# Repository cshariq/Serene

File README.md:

# SERENE

Can't hear your friend talking on the highway? Do you need to blast your music just to hear it well? Well, you're in luck, because **Serene** is a portable noise-cancelling device that can remove all of that noise!

Just stick it to the roof of your car, and Serene will capture the road noise and output sounds waves that cancel them out, so that you can enjoy a peaceful car ride. 

Serene is a small, portable device that connects directly to your phone and car speaker. It sticks seamlessly to the walls of your car, and using ANC algorithms, it minimizes the external noise that it picks up inside the car.  

---

## Inspiration 

During family road trips, I sat in the backseat as a child, and if I didn't yell, my parents in the front couldn't hear me. This was so annoying, as a long highway drive almost always came with losing my voice. 

With my dad's hearing getting worse, I figured that we needed a way to drown out the road noise. I was desparate for a solution, so taking inspiration from noise-cancelling technology in headphones, I thought: "What if we did the same thing in cars?". 

While a few very luxury cars offer ANC, I wanted to make ANC more accessible to all people, because everyone deserves sereneness!

---

## How to use Serene

1. Click the power ON button at the top of the casing. 
2. Download the Serene app and pair your mobile device through Bluetooth / AUX / USB. 
3. Proceed with the calibration process.
4. Stick the Serene device anywhere in your car.
5. Turn the car on and start your peaceful drive.

---

## 3D Model: [OnShape Link](https://cad.onshape.com/documents/61c8b07b134ed299bc7b3a3e/w/ec2ebddc7aaece6417831267/e/c16017c5fc26cf24515a7a41?renderMode=0&uiState=69a0cfd834c79f4888558db4)

### PCB:

### Casing:

---

## PCB
### Main PCB

### Button PCB

---

## Wiring Diagram
### Main PCB

### Button PCB

---

## BOM
| Quantity | Part Name                               | Compoenent                                                    | Price(1 Quantity) | Total Price for all quantiy | Link                                                                              | Status    |
|----------|-----------------------------------------|---------------------------------------------------------------|-------------------|-----------------------------|-----------------------------------------------------------------------------------|-----------|
| 1        | WQFN-HR18__RYK_TEX                      | Power Chip                                                    | $2.48             | $2.48                       | https://jlcpcb.com/partdetail/TexasInstruments-BQ25620RYKR/C6164243               | In Stock  |
| 2        | CONN_X.FL-R-SMT-180_HIR                 | Coaxial Connector for bluetooth and UWB antennas              | $0.27             | $0.53                       | https://jlcpcb.com/partdetail/HRS_Hirose-X_FL_R_SMT_1_80/C434819                  | In Stock  |
| 17       | C_0402_1005Metric                       | Capacitor, 0.1uF                                              | $0.00             | $0.03                       | https://jlcpcb.com/partdetail/MurataElectronics-GRM155R71C104KA88D/C71629         | In Stock  |
| 1        | C_0402_1005Metric                       | Capacitor, 47nF                                               | $0.00             | $0.00                       | https://jlcpcb.com/partdetail/MurataElectronics-GRM155R71E473KA88D/C77017         | In Stock  |
| 1        | Spark_SR1120_QFN32                      | UWB Chip, used for audio transmission                         | $16.54            | $16.54                      | https://jlcpcb.com/partdetail/SPARKMicrosystems-SR1120AA_4Q32TR/C47090725         | Pre-Order |
| 1        | SOT-23-5                                | 1.8V Power Regulator                                          | $0.11             | $0.11                       | https://jlcpcb.com/partdetail/DiodesIncorporated-AP2112K_18TRG1/C176944           | In Stock  |
| 2        | Infineon_PG-LLGA-5-2                    | Mics                                                          | $10.28            | $20.56                      | https://www.aliexpress.com/item/1005009306016183.html?gatewayAdapt=4itemAdapt                                | In Stock  |
| 1        | USB_C_Receptacle_GCT_USB4085            | USB C Port (USB 2.0)                                          | $1.19             | $1.19                       | https://jlcpcb.com/partdetail/8061907-USB4085_GFA/C7095263                        | In Stock  |
| 1        | Jack_3.5mm_CUI_SJ2-3593D-SMT_Horizontal | Headphone Jack                                                | $11.30            | $11.30                      | https://jlcpcb.com/partdetail/CUI-SJ2_3593D_SMTTR/C4991621                        | In Stock  |
| 4        | R_0402_1005Metric                       | Resistor, 100kΩ                                               | $0.01             | $0.04                       | https://jlcpcb.com/partdetail/YAGEO-RC0402FR07100KL/C60491                        | In Stock  |
| 1        | STM32H743ZIT6                           | Microcontroller, STM32H743ZIT6                                | $8.19             | $8.19                       | https://jlcpcb.com/partdetail/STMicroelectronics-STM32H743ZIT6/C114408            | In Stock  |
| 7        | C_0402_1005Metric                       | Capacitor, 10uF                                               | $0.01             | $0.07                       | https://jlcpcb.com/partdetail/MurataElectronics-GRM155R60J106ME44D/C76991         | In Stock  |
| 1        | C_0402_1005Metric                       | Capacitor, 4.7µF                                              | $0.01             | $0.01                       | https://jlcpcb.com/partdetail/313626-GRM155R61A475MEAAD/C335105                   | In Stock  |
| 1        | ADXL382_Ultralib                        | Vibration Sensor, used for predicting sound                   | $28.05            | $28.05                      | https://jlcpcb.com/partdetail/AnalogDevices-ADXL382_1BCCZRL7/C41718413            | In Stock  |
| 1        | L_0603_1608Metric                       | Inductor, 180nH                                               | $0.09             | $0.09                       | https://jlcpcb.com/partdetail/MurataElectronics-LQW18ANR18G80D/C162650            | In Stock  |
| 1        | Crystal_SMD_3225-4Pin_3.2x2.5mm         | Crystal, 32.768 kHz                                           | $0.49             | $0.49                       | https://jlcpcb.com/partdetail/AbraconLLC-ABS07_32_768KHZT/C130253                 | In Stock  |
| 5        | C_0402_1005Metric                       | Capacitor, 1uF                                                | $0.01             | $0.05                       | https://jlcpcb.com/partdetail/MurataElectronics-GRM155R61A105KE15D/C76999         | In Stock  |
| 6        | C_0402_1005Metric                       | Capacitor, 10pF                                               | $0.01             | $0.06                       | https://jlcpcb.com/partdetail/MurataElectronics-GRM1555C1H100JA01D/C76946         | In Stock  |
| 1        | ADAU1787_Ultralib                       | DSP(Digital Signal Processor) used for processing sound       | $19.07            | $19.07                      | https://jlcpcb.com/partdetail/AnalogDevices-ADAU1787BCBZRL7/C3226201              | In Stock  |
| 1        | SOT-223-3_TabPin2                       | 3.3V Power Regulator                                          | $0.29             | $0.29                       | https://jlcpcb.com/partdetail/DiodesIncorporated-AP7361C_33E13/C500795            | In Stock  |
| 2        | R_0402_1005Metric                       | Resistor, 5.1k                                                | $0.01             | $0.02                       | https://jlcpcb.com/partdetail/YAGEO-RC0402FR075K1L/C105872                        | In Stock  |
| 1        | L_0603_1608Metric                       | Inductor, 1.5uH                                               | $0.10             | $0.10                       | https://jlcpcb.com/partdetail/MurataElectronics-DFE252012F_1R5MP2/C909806         | In Stock  |
| 1        | BGM220S_SIL                             | Bluetooth Chip                                                | $13.84            | $13.84                      | https://jlcpcb.com/partdetail/1603489-BGM220SC12WGA2R/C1512693                    | Pre-Order |
| 1        | Crystal_SMD_3225-4Pin_3.2x2.5mm         | Crystal                                                       | $0.08             | $0.08                       | https://jlcpcb.com/partdetail/YXC_CrystalOscillators-X322525MQB4SI/C70585         | In Stock  |
| 1        | Balun_Johanson_1.6x0.8mm                | Transformer                                                   | $8.97             | $8.97                       | https://jlcpcb.com/partdetail/YXC_CrystalOscillators-X322525MQB4SI/C70585         | In Stock  |
| 2        | R_0402_1005Metric                       | Resistor, 2.2kΩ                                               | $0.01             | $0.02                       | https://jlcpcb.com/partdetail/YAGEO-RC0402FR072K2L/C114762                        | In Stock  |
| 1        | R_0402_1005Metric                       | Resistor, 170Ω                                                | $0.01             | $0.01                       | https://jlcpcb.com/partdetail/YAGEO-RC0402FR07180RL/C138045                       | In Stock  |
| 5        | R_0402_1005Metric                       | Resistor, 10kΩ                                                | $0.01             | $0.05                       | https://jlcpcb.com/partdetail/YAGEO-RC0402FR0710KL/C60490                         | In Stock  |
| 2        | C_0402_1005Metric                       | Capacitor, 2.2uF                                              | $0.01             | $0.02                       | https://jlcpcb.com/partdetail/MurataElectronics-GRM155R61A225KE95D/C77002         | In Stock  |
| 1        | SOT-23-6                                | ESD protection diode, used for headphone jack                 | $0.13             | $0.13                       | https://jlcpcb.com/partdetail/STMicroelectronics-USBLC62SC6/C7519                 | In Stock  |
| 2        | CONN_503480-0540_MOL                    | Molex connector used for linking button PCB with main PCB     | $0.83             | $1.66                       | https://jlcpcb.com/partdetail/MOLEX-5034800540/C5527934                           | In Stock  |
| 3        | LED_SK6805_PLCC4_2.4x2.7mm_P1.3mm       | LEDS on the Button PCB                                        | $3.95             | $11.86                      | https://www.adafruit.com/product/4492                                             | In Stock  |
| 1        | SW_Push_1P1T_NO_CK_KMR2                 | Button on the Button PCB                                      | $0.61             | $0.61                       | https://jlcpcb.com/partdetail/CK-KMR221GLFS/C72443                                | In Stock  |
| 1        | Vapcell N40                             | Battery                                                       | $20.00            | $20.00                      | https://www.vapcelltech.com/h-pd-193.html                                         | In Stock  |
| 1        | N/A                                     | Nickel Strips used for connecting the + and - of the battery  | $6.45             | $6.45                       | https://www.amazon.ca/Nickel-Plated-Connection-Refined-Welding/dp/B0CPFL5ZWM/     | In Stock  |
| 1        | N/A                                     | Pair of Pogo Pins                                             | $6.06             | $6.06                       | https://www.amazon.ca/Connector-Positions-Pogopin-Contact-3PIN/dp/B0BXDFJVVZ?th=1 | In Stock  |
| 1        | N/A                                     | uxcell 45mm x 0.5mm 6 Pin FPC/FFC Flat Ribbon Cable Connector | $9.99             | $9.99                       | https://www.amazon.ca/gp/product/B00H8PCW06                                       |           |
| 1        | N/A                                     | N/A                                                           | $53.85            | $53.85                      |                                                                                   |           |
| 1        | N/A                                     | N/A                                                           | $7.20             | $7.20                       |                                                                                   |           |

| Subtotal               | Source       | Notes                                                                                                                                                                    |
|------------------------|--------------|--------------------------------------------------------------------------------------------------------------------------------------------------------------------------|
| $228.21                | JLCPCB Parts | 2x (JLCPCB requires 2 of each part)                                                                                                                                      |
| $61.05                 | JLCPCB PCB   | 0.15mm via and epoxy filled & capped selectedas it is required by the ADAU1787 Chip. Lead free coating also selected for safety and its only a dollar extra. 6 Layer manufacturing is selected because it is cheaper than 2/4 layer manufacturing due to a coupon. Although other options were explored, most DSPs(Digital Singal Processors) which is required for fast processing of audio(required for ANC) are WLCSP chips requiring 0.15mm vias which are epoxy filled & capped. Other solutions are too slow for this application.|
| $22.50                 | Amazon       |                                                                                                                                                                          |
| $20.56                 | AliExpress   |                                                                                                                                                                          |
| $11.86                 | Adafruit     | For the LEDs                                                                                                                                                             |
| $250.08                | All          | Not accounting for 2x JLCPCB Parts                                                                                                                                       |
| $364.18                | All          | 2x (JLCPCB required 2 of each part)                                                                                                                                      |

| Grand Total            | Price        | Notes                                                                                                                                                                    |
|------------------------|--------------|--------------------------------------------------------------------------------------------------------------------------------------------------------------------------|
| JLCParts Grand Total   | $238.13      | 2x (JLCPCB required 2 of each part)                                                                                                                                      |
| JLCPCB Grand Total     | $72.25       | JLCPCB Advanced is cheaper due to coupons                                                                                                                                |
| Amazon Subtotal        | $16.28       | 22.5 CAD --> 16.28 USD                                                                                                                                                   |
| Adafruit Grand Total   | $23.08       |                                                                                                                                                                          |
| AliExpress Grand Total | $20.70       | 28.07 CAD --> 20.70 USD                                                                                                                                                  |
| Vapcell Grand Total    | $22.99       |                                                                                                                                                                          |
| Grand Total            | $393.43      |                                                                                                                                                                          |

### Screenshots of total with shipping and taxes.

Amazon:

JLCPCB Parts:

JLCPCB PCB (6 layer manufacturing for Main PCB, less expensive):

JLCPCB PCB (4 layer manufacturing for Main PCB, more expensive and thus **not used**)

Button PCB:

AliExpress:

Vapcell:

Adafruit:

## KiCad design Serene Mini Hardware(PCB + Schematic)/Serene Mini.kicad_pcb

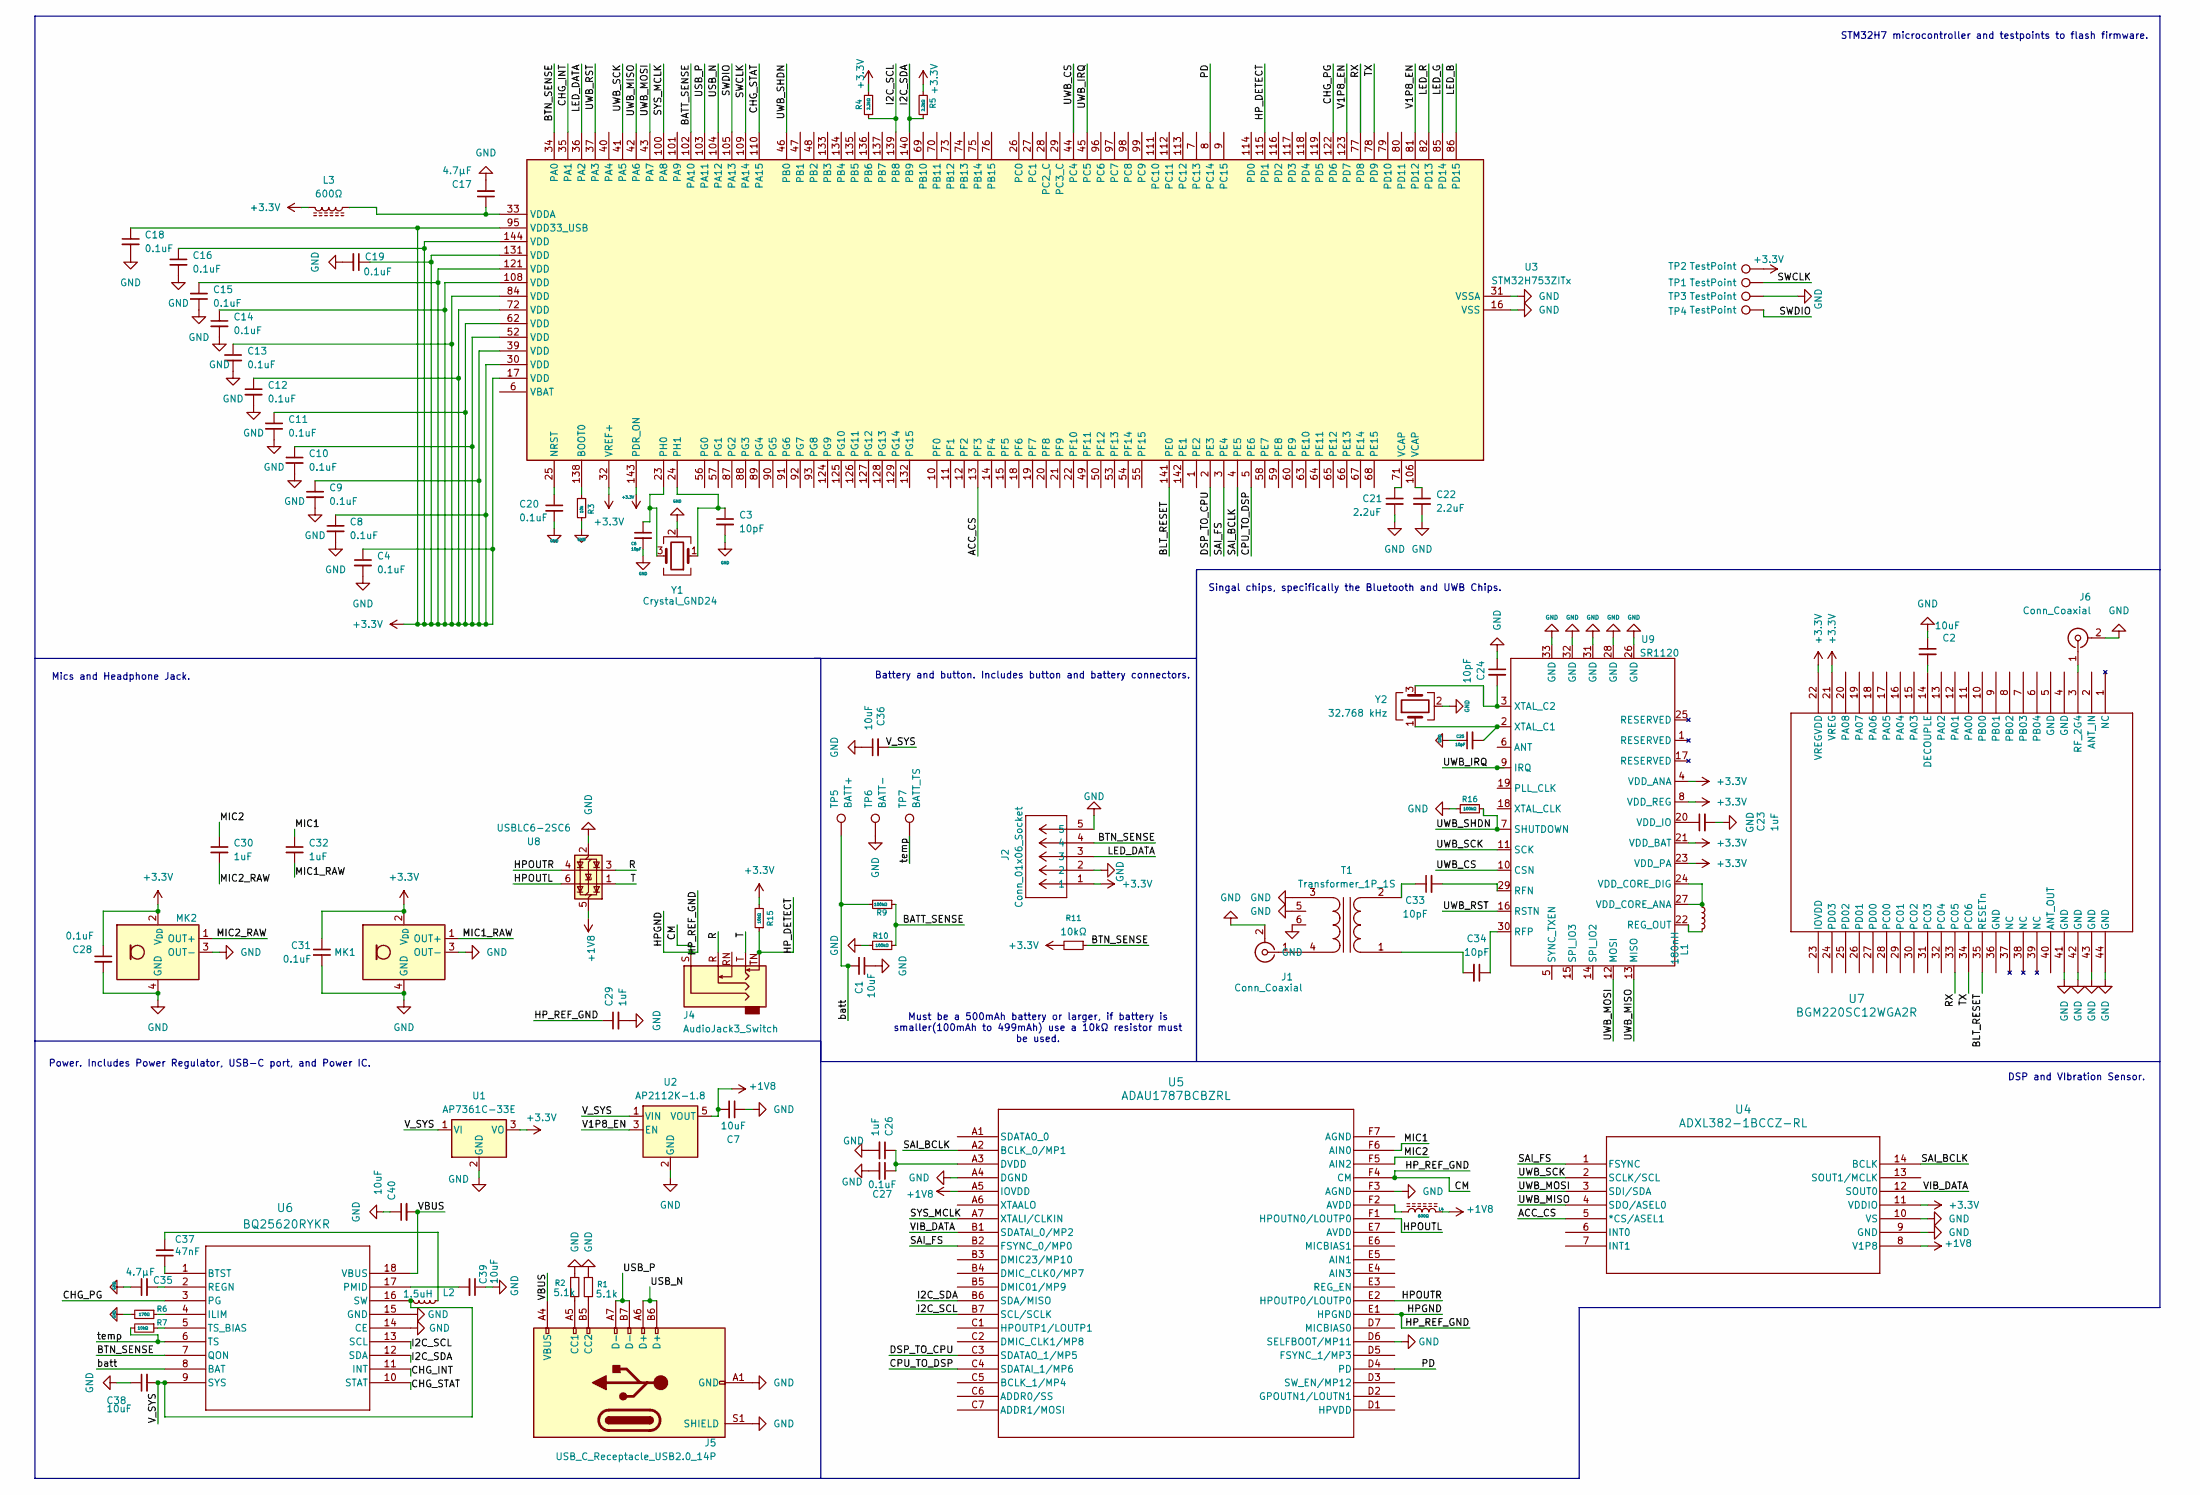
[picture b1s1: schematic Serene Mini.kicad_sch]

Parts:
C1, C2, C7, C36, C38, C39, C40: 10uF; C_0402_1005Metric
C3, C6, C24, C25, C33, C34: 10pF; C_0402_1005Metric
C4, C8, C9, C10, C11, C12, C13, C14, C15, C16, C18, C19, C20, C27, C28, C31: 0.1uF; C_0402_1005Metric
C17, C35: 4.7µF; C_0402_1005Metric
C21, C22: 2.2uF; C_0402_1005Metric
C23, C26, C29, C30, C32: 1uF; C_0402_1005Metric
C37: 47nF; C_0402_1005Metric
J1, J6: Conn_Coaxial; CONN_X.FL-R-SMT-180_HIR
J2: Conn_01x06_Socket; CONN_503480-0540_MOL
J4: AudioJack3_Switch; Jack_3.5mm_CUI_SJ2-3593D-SMT_Horizontal
J5: USB_C_Receptacle_USB2.0_14P; USB_C_Receptacle_GCT_USB4085
L1: 180nH; L_0603_1608Metric
L2: 1.5uH; L_0603_1608Metric
L3, L4: 600Ω; L_0402_1005Metric
MK1, MK2: IM73A135V01; Infineon_PG-LLGA-5-2
R1, R2: 5.1k; R_0402_1005Metric
R3: 10k; R_0402_1005Metric
R4, R5: 2.2kΩ; R_0402_1005Metric
R6: 170Ω; R_0402_1005Metric
R7, R11, R15: 10kΩ; R_0402_1005Metric
R9, R10, R16: 100kΩ; R_0402_1005Metric
T1: Transformer_1P_1S; Balun_Johanson_1.6x0.8mm
TP1, TP2, TP3, TP4: TestPoint; TestPoint_Pad_1.0x1.0mm
TP5: BATT+; SolderWirePad_1x01_SMD_1x2mm
TP6: BATT-; SolderWirePad_1x01_SMD_1x2mm
TP7: BATT_TS; SolderWirePad_1x01_SMD_1x2mm
U1: AP7361C-33E; SOT-223-3_TabPin2
U2: AP2112K-1.8; SOT-23-5
U3: STM32H753ZITx; LQFP-144_20x20mm_P0.5mm
U4: ADXL382-1BCCZ-RL; ADXL382_Ultralib
U5: ADAU1787BCBZRL; ADAU1787_Ultralib
U6: BQ25620RYKR; WQFN-HR18__RYK_TEX
U7: BGM220SC12WGA2R; BGM220S_SIL
U8: USBLC6-2SC6; SOT-23-6
U9: SR1120; Spark_SR1120_QFN32
Y1: Crystal_GND24; Crystal_SMD_3225-4Pin_3.2x2.5mm
Y2: 32.768 kHz; Crystal_SMD_3225-4Pin_3.2x2.5mm

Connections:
+1V8: C7.2, L4.2, U2.5 (VOUT), U4.8 (V1P8), U5.A5 (IOVDD), U8.5 (VBUS)
+3.3V: C4.1, C8.1, C9.1, C10.1, C11.1, C12.1, C13.1, C14.1, C15.1, C16.1, C18.1, C19.1, C28.1, C31.1, J2.1, L3.2, MK1.2 (V_{DD}), MK2.2 (V_{DD}), R4.2, R5.2, R11.2, R15.2, TP1.1, U1.3 (VO), U3.17 (VDD), U3.30 (VDD), U3.32 (VREF+), U3.39 (VDD), U3.52 (VDD), U3.62 (VDD), U3.72 (VDD), U3.84 (VDD), U3.95 (VDD33_USB), U3.108 (VDD), U3.121 (VDD), U3.131 (VDD), U3.143 (PDR_ON), U3.144 (VDD), U4.11 (VDDIO), U7.21 (VREG), U7.22 (VREGVDD), U9.4 (VDD_ANA), U9.8 (VDD_REG), U9.21 (VDD_BAT), U9.23 (VDD_PA)
/ACC_CS: U3.13 (PF3), U4.5 (*CS/ASEL1)
/BATT_SENSE: R9.1, R10.1, U3.102 (PA10)
/BLT_RESET: U3.141 (PE0), U7.35 (RESETn)
/BTN_SENSE: J2.4, R11.1, U3.34 (PA0), U6.7 (QON)
/CHG_INT: U3.35 (PA1), U6.11 (INT)
/CHG_PG: U3.122 (PD6), U6.3 (PG)
/CHG_STAT: U3.110 (PA15), U6.10 (STAT)
/CM: C29.1, J4.S, U5.E1 (HPGND), U5.F4 (CM)
/CPU_TO_DSP: U3.5 (PE6), U5.C4 (SDATAI_1/MP6)
/DSP_TO_CPU: U3.2 (PE3), U5.C3 (SDATAO_1/MP5)
/HPOUTL: U5.F1 (HPOUTN0/LOUTP0), U8.6 (I/O1)
/HPOUTR: U5.E2 (HPOUTP0/LOUTP0), U8.4 (I/O2)
/HP_DETECT: J4.TN, R15.1, U3.115 (PD1)
/I2C_SCL: R4.1, U3.139 (PB8), U5.B7 (SCL/SCLK), U6.13 (SCL)
/I2C_SDA: R5.1, U3.140 (PB9), U5.B6 (SDA/MISO), U6.12 (SDA)
/LED_B: U3.86 (PD15)
/LED_DATA: J2.3, U3.36 (PA2)
/LED_G: U3.85 (PD14)
/LED_R: U3.82 (PD13)
/MIC1: C32.1, U5.F6 (AIN0)
/MIC1_RAW: C32.2, MK1.1 (OUT+)
/MIC2: C30.1, U5.F5 (AIN2)
/MIC2_RAW: C30.2, MK2.1 (OUT+)
/PD: U3.8 (PC14), U5.D4 (PD)
/R: J4.R, U8.3 (I/O2)
/RX: U3.77 (PD8), U7.33 (PC05)
/SAI_BCLK: U3.4 (PE5), U4.14 (BCLK), U5.A2 (BCLK_0/MP1)
/SAI_FS: U3.3 (PE4), U4.1 (FSYNC), U5.B2 (FSYNC_0/MP0)
/SWCLK: TP2.1, U3.109 (PA14)
/SWDIO: TP4.1, U3.105 (PA13)
/SYS_MCLK: U3.100 (PA8), U5.A7 (XTALI/CLKIN)
/T: J4.T, U8.1 (I/O1)
/TX: U3.78 (PD9), U7.34 (PC06)
/USB_N: J5.A6 (D+), J5.B6 (D+), U3.104 (PA12)
/USB_P: J5.A7 (D-), J5.B7 (D-), U3.103 (PA11)
/UWB_CS: U3.44 (PC4), U9.10 (CSN)
/UWB_IRQ: U3.45 (PC5), U9.9 (IRQ)
/UWB_MISO: U3.42 (PA6), U4.4 (SDO/ASEL0), U9.13 (MISO)
/UWB_MOSI: U3.43 (PA7), U4.3 (SDI/SDA), U9.12 (MOSI)
/UWB_RST: U3.37 (PA3), U9.16 (RSTN)
/UWB_SCK: U3.41 (PA5), U4.2 (SCLK/SCL), U9.11 (SCK)
/UWB_SHDN: R16.2, U3.46 (PB0), U9.7 (SHUTDOWN)
/V1P8_EN: U2.3 (EN), U3.81 (PD12), U3.123 (PD7)
/VBUS: C40.2, J5.A4 (VBUS), J5.A9 (VBUS), J5.B4 (VBUS), J5.B9 (VBUS), U6.18 (VBUS)
/VIB_DATA: U4.12 (SOUT0), U5.B1 (SDATAI_0/MP2)
/V_SYS: C36.2, C38.2, L2.2, U1.1 (VI), U2.1 (VIN), U6.9 (SYS), U6.16 (SW)
/batt: C1.2, R9.2, TP5.1, U6.8 (BAT)
/temp: R7.2, TP7.1, U6.6 (TS)
GND: C1.1, C2.1, C3.2, C4.2, C6.2, C7.1, C8.2, C9.2, C10.2, C11.2, C12.2, C13.2, C14.2, C15.2, C16.2, C17.2, C18.2, C19.2, C20.2, C21.2, C22.2, C23.2, C24.1, C25.1, C26.2, C27.2, C28.2, C29.2, C31.2, C35.1, C36.1, C38.1, C39.1, C40.1, J1.2 (Ext), J2.2, J2.5, J5.A1 (GND), J5.A12 (GND), J5.B1 (GND), J5.B12 (GND), J5.S1 (SHIELD), J6.2 (Ext), MK1.3 (OUT-), MK1.4 (GND), MK1.5 (GND), MK2.3 (OUT-), MK2.4 (GND), MK2.5 (GND), R1.1, R2.1, R3.2, R6.2, R10.2, R16.1, T1.3 (SA), T1.5 (GND), T1.6 (GND), TP3.1, TP6.1, U1.2 (GND), U2.2 (GND), U3.16 (VSS), U3.31 (VSSA), U3.38 (VSS), U3.51 (VSS), U3.61 (VSS), U3.83 (VSS), U3.94 (VSS), U3.107 (VSS), U3.120 (VSS), U3.130 (VSS), U4.9 (GND), U4.10 (VS), U5.A4 (DGND), U5.D6 (SELFBOOT/MP11), U5.F3 (AGND), U6.1 (BTST), U6.5 (TS_BIAS), U6.10 (STAT), U6.14 (CE), U6.15 (GND), U7.41 (GND), U7.42 (GND), U7.43 (GND), U7.44 (GND), U8.2 (GND), U9.26 (GND), U9.28 (GND), U9.31 (GND), U9.32 (GND), U9.33 (GND), Y1.2 (G), Y1.4 (G), Y2.2 (G), Y2.4 (G)
unnamed: C21.1, U3.71 (VCAP)
unnamed: C22.1, U3.106 (VCAP)
unnamed: C37.2, L2.1
unnamed: J1.1 (In), T1.4 (SB)
unnamed: J5.A5 (CC1), R2.2
unnamed: J5.B5 (CC2), R1.2
unnamed: J6.1 (In), U7.3 (RF_2G4)
unnamed: L4.1, U5.F2 (AVDD)
unnamed: C34.2, T1.1 (AA)
unnamed: C33.1, T1.2 (AB)
unnamed: R3.1, U3.138 (BOOT0)
unnamed: C20.1, U3.25 (NRST)
unnamed: C6.1, U3.23 (PH0), Y1.3
unnamed: C3.1, U3.24 (PH1), Y1.1
unnamed: C17.1, L3.1, U3.33 (VDDA)
unnamed: C26.1, C27.1, U5.A3 (DVDD)
unnamed: C37.1, U6.1 (BTST)
unnamed: R6.1, U6.4 (ILIM)
unnamed: C39.2, U6.17 (PMID)
unnamed: C35.2, U6.2 (REGN)
unnamed: R7.1, U6.5 (TS_BIAS)
unnamed: C2.2, U7.14 (DECOUPLE)
unnamed: L1.2, U9.22 (REG_OUT)
unnamed: C33.2, U9.29 (RFN)
unnamed: C34.1, U9.30 (RFP)
unnamed: L1.1, U9.24 (VDD_CORE_DIG), U9.27 (VDD_CORE_ANA)
unnamed: C23.1, U9.20 (VDD_IO)
unnamed: C25.2, U9.2 (XTAL_C1), Y2.1
unnamed: C24.2, U9.3 (XTAL_C2), Y2.3

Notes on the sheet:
Must be a 500mAh battery or larger, if battery is smaller(100mAh to 499mAh) use a 10kΩ resistor must be used.
STM32H7 microcontroller and testpoints to flash firmware.
Battery and button. Includes button and battery connectors.
DSP and VIbration Sensor.
Power. Includes Power Regulator, USB-C port, and Power IC.
Singal chips, specifically the Bluetooth and UWB Chips.
Mics and Headphone Jack.

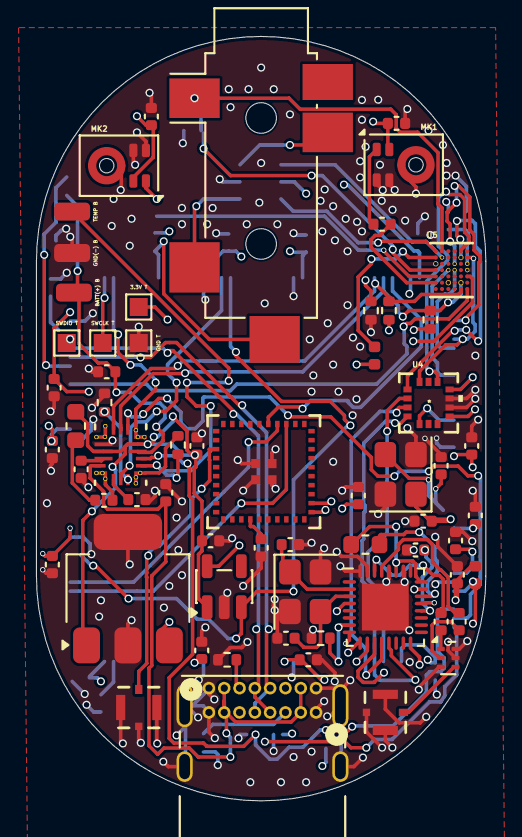
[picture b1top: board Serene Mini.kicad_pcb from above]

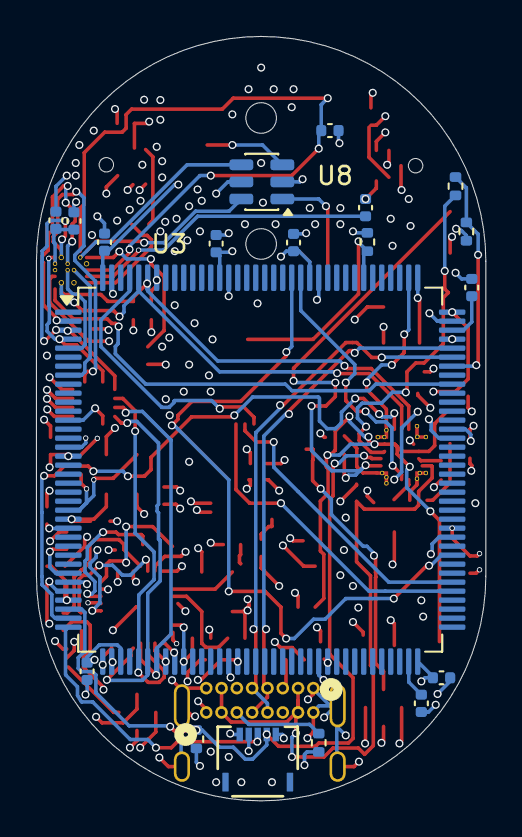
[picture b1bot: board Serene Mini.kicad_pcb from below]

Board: 6 copper layers, 25.0 x 42.5 mm, 81 parts (19 on the bottom side), 77 nets.

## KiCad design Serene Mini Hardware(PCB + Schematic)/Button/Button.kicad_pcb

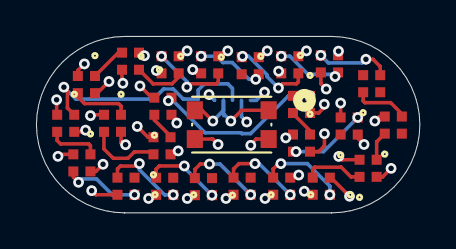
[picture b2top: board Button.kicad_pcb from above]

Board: 4 copper layers, 21.3 x 9.8 mm, 26 parts (1 on the bottom side), 27 nets.

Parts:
D1, D2, D3, D4, D5, D6, D7, D8, D9, D10, D11, D12, D13, D14, D15, D16, D17, D18, D19, D20, D21, D22, D23, D24: SK6805; IPIXEL SK6805-E-J_ADA
J2: Conn_01x06_Socket; CONN_503480-0540_MOL
SW1: SW_Push; SW_Push_1P1T_NO_CK_KMR2

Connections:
+3.3V: D1.2 (VDD), D2.2 (VDD), D3.2 (VDD), D4.2 (VDD), D5.2 (VDD), D6.2 (VDD), D7.2 (VDD), D8.2 (VDD), D9.2 (VDD), D10.2 (VDD), D11.2 (VDD), D12.2 (VDD), D13.2 (VDD), D14.2 (VDD), D15.2 (VDD), D16.2 (VDD), D17.2 (VDD), D18.2 (VDD), D19.2 (VDD), D20.2 (VDD), D21.2 (VDD), D22.2 (VDD), D23.2 (VDD), D24.2 (VDD), J2.1
/BTN_SENSE: J2.4, SW1.1
/LED_DATA: D1.1 (DIN), J2.3
GND: D1.4 (GND), D2.4 (GND), D3.4 (GND), D4.4 (GND), D5.4 (GND), D6.4 (GND), D7.4 (GND), D8.4 (GND), D9.4 (GND), D10.4 (GND), D11.4 (GND), D12.4 (GND), D13.4 (GND), D14.4 (GND), D15.4 (GND), D16.4 (GND), D17.4 (GND), D18.4 (GND), D19.4 (GND), D20.4 (GND), D21.4 (GND), D22.4 (GND), D23.4 (GND), D24.4 (GND), J2.2, J2.5, SW1.2
unnamed: D1.3 (DOUT), D2.1 (DIN)
unnamed: D2.3 (DOUT), D3.1 (DIN)
unnamed: D3.3 (DOUT), D4.1 (DIN)
unnamed: D4.3 (DOUT), D5.1 (DIN)
unnamed: D5.3 (DOUT), D6.1 (DIN)
unnamed: D6.3 (DOUT), D7.1 (DIN)
unnamed: D7.3 (DOUT), D8.1 (DIN)
unnamed: D8.3 (DOUT), D9.1 (DIN)
unnamed: D9.3 (DOUT), D10.1 (DIN)
unnamed: D10.3 (DOUT), D11.1 (DIN)
unnamed: D11.3 (DOUT), D12.1 (DIN)
unnamed: D12.3 (DOUT), D13.1 (DIN)
unnamed: D13.3 (DOUT), D14.1 (DIN)
unnamed: D14.3 (DOUT), D15.1 (DIN)
unnamed: D15.3 (DOUT), D16.1 (DIN)
unnamed: D16.3 (DOUT), D17.1 (DIN)
unnamed: D17.3 (DOUT), D18.1 (DIN)
unnamed: D18.3 (DOUT), D19.1 (DIN)
unnamed: D19.3 (DOUT), D20.1 (DIN)
unnamed: D20.3 (DOUT), D21.1 (DIN)
unnamed: D21.3 (DOUT), D22.1 (DIN)
unnamed: D22.3 (DOUT), D23.1 (DIN)
unnamed: D23.3 (DOUT), D24.3 (DOUT)

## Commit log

2025-12-22 Created Structure for Dart App
2025-12-22 Initial App UI
2025-12-23 Updated UI
2025-12-24 Bug Fixes
2025-12-28 Redesigned vehicle and sound menu
2026-01-05 Implement vehicle selection screen with custom vehicle addition
    - Added VehicleSelectionScreen for selecting and adding vehicles.
    - Integrated search functionality for vehicle models.
    - Implemented dialog for adding custom vehicles with type selection.
    - Enhanced vehicle selection logic with existing vehicle handling.
    - Added validation for device limits based on vehicle type.
    Introduce ANC audio output service
2026-01-13 Add GitHub Actions workflow for Dart CI
2026-01-13 Update dart.yml to include path filters
    Add path filters for push and pull_request events
2026-01-13 Update dart.yml to include paths for serene directory
    Specify paths for push and pull_request events.
2026-01-13 Update README to remove introductory line
    Removed introductory line about the project being a new Flutter project.
2026-01-13 Refactor Dart CI workflow for clarity and structure
2026-01-13 Add project description to README
    Added a brief description of the project.
2026-01-13 Switch Dart commands to Flutter in CI workflow
2026-01-13 Update Dart workflow to use Flutter setup
2026-01-13 Fix formatting in README.md
2026-01-15 Refactor Flutter CI/CD workflow for better structure
2026-01-19 Added support for battery
2026-01-20 PCB and Schematic Design Changes
    Upgraded to the newer sr1120
    Reduced the PCB size by ~40%
    More efficient layout with chips on both side of the pcb
2026-01-23 Final PCB and Schematic Design
    - Added new IC to support fast charging for batteries up to 3000mAh
    - Added a bluetooth chip
    - Used smaller coaxial ports to increase available space
    - The button is now located off the board connected via molax
    - Finished routing
2026-01-23 PCB Fixes
    Connected some missing traces and fixed some clearance issues
2026-01-23 Footprint Fixes
    Added/linked a 3D model to the molex connector.
2026-01-23 Changed Footprint
    Added cooling and repositioned the testpoint pads to be closer ti each other
2026-01-28 Minor Changes
    - Fixed minor issues in the PCB like routing the USB data lines parallel
    - Added BOM
    - Added blueprint folder containing everything required
2026-01-28 Added Checkout Screenshots
2026-01-28 Added Documentation and Drill files
2026-02-02 Minor Changes
2026-02-05 Add initial README for Serene
    Added a detailed description of the Serene noise-cancelling device, including its inspiration, usage instructions, and sections for 3D model, PCB, wiring diagram, and BOM.
2026-02-05 Clean up README formatting
    Removed extra line breaks in PCB and Wiring Diagram sections.
2026-02-05 Add images for PCB and Casing in README
    Added images for PCB and Casing sections in README.
2026-02-05 fixed formatting
2026-02-05 Add detailed BOM to README
    Added a detailed Bill of Materials (BOM) with component specifications, quantities, prices, and sources.
2026-02-05 fixed formatting #2
2026-02-05 File Structure Changes
2026-02-05 change image sizes
2026-02-06 Enhance PCB selection explanation in README
    Expanded details on PCB selection and alternatives for DSPs.
2026-02-06 Revise PCB cost details and format screenshots section
    Updated PCB manufacturing details and changed heading format for screenshots.
2026-02-06 Update PCB manufacturing description in README
2026-02-06 Clean up image entries in README.md
    Removed unnecessary image entries from the README.
2026-02-06 Add supplier screenshots to README
    Added screenshots for various suppliers including Amazon, AliExpress, Vapcell, and Adafruit.
2026-02-06 Add images and descriptions to README
2026-02-06 Add grand total section to README
2026-02-06 Update 'Source' to 'Price' in README table
2026-02-06 Revise JLCPCB PCB descriptions in README
    Updated descriptions for JLCPCB PCB images to clarify manufacturing layers and costs.
2026-02-06 Changes to File Structure
    - Removed redundant blueprint folder
    - Made folder names more clear
2026-02-07 Added Stitching Vias
2026-02-07 Changes to PCB
    - Added 2 more filled zones, 1 on layer 3 and 4 respectively
    - Added stitching vias
    - Fixed some DRC Issues
2026-02-08 Fixed Issues with PCB
2026-02-08 Add new PCB image to README
2026-02-09 Update README with PCB and Wiring Diagram sections
    Added PCB and Wiring Diagram sections with images to README.
2026-02-09 Update README.md to remove duplicate image
    Removed duplicate image and adjusted layout for Button PCB section.
2026-02-27 Add OnShape link for 3D model in README
